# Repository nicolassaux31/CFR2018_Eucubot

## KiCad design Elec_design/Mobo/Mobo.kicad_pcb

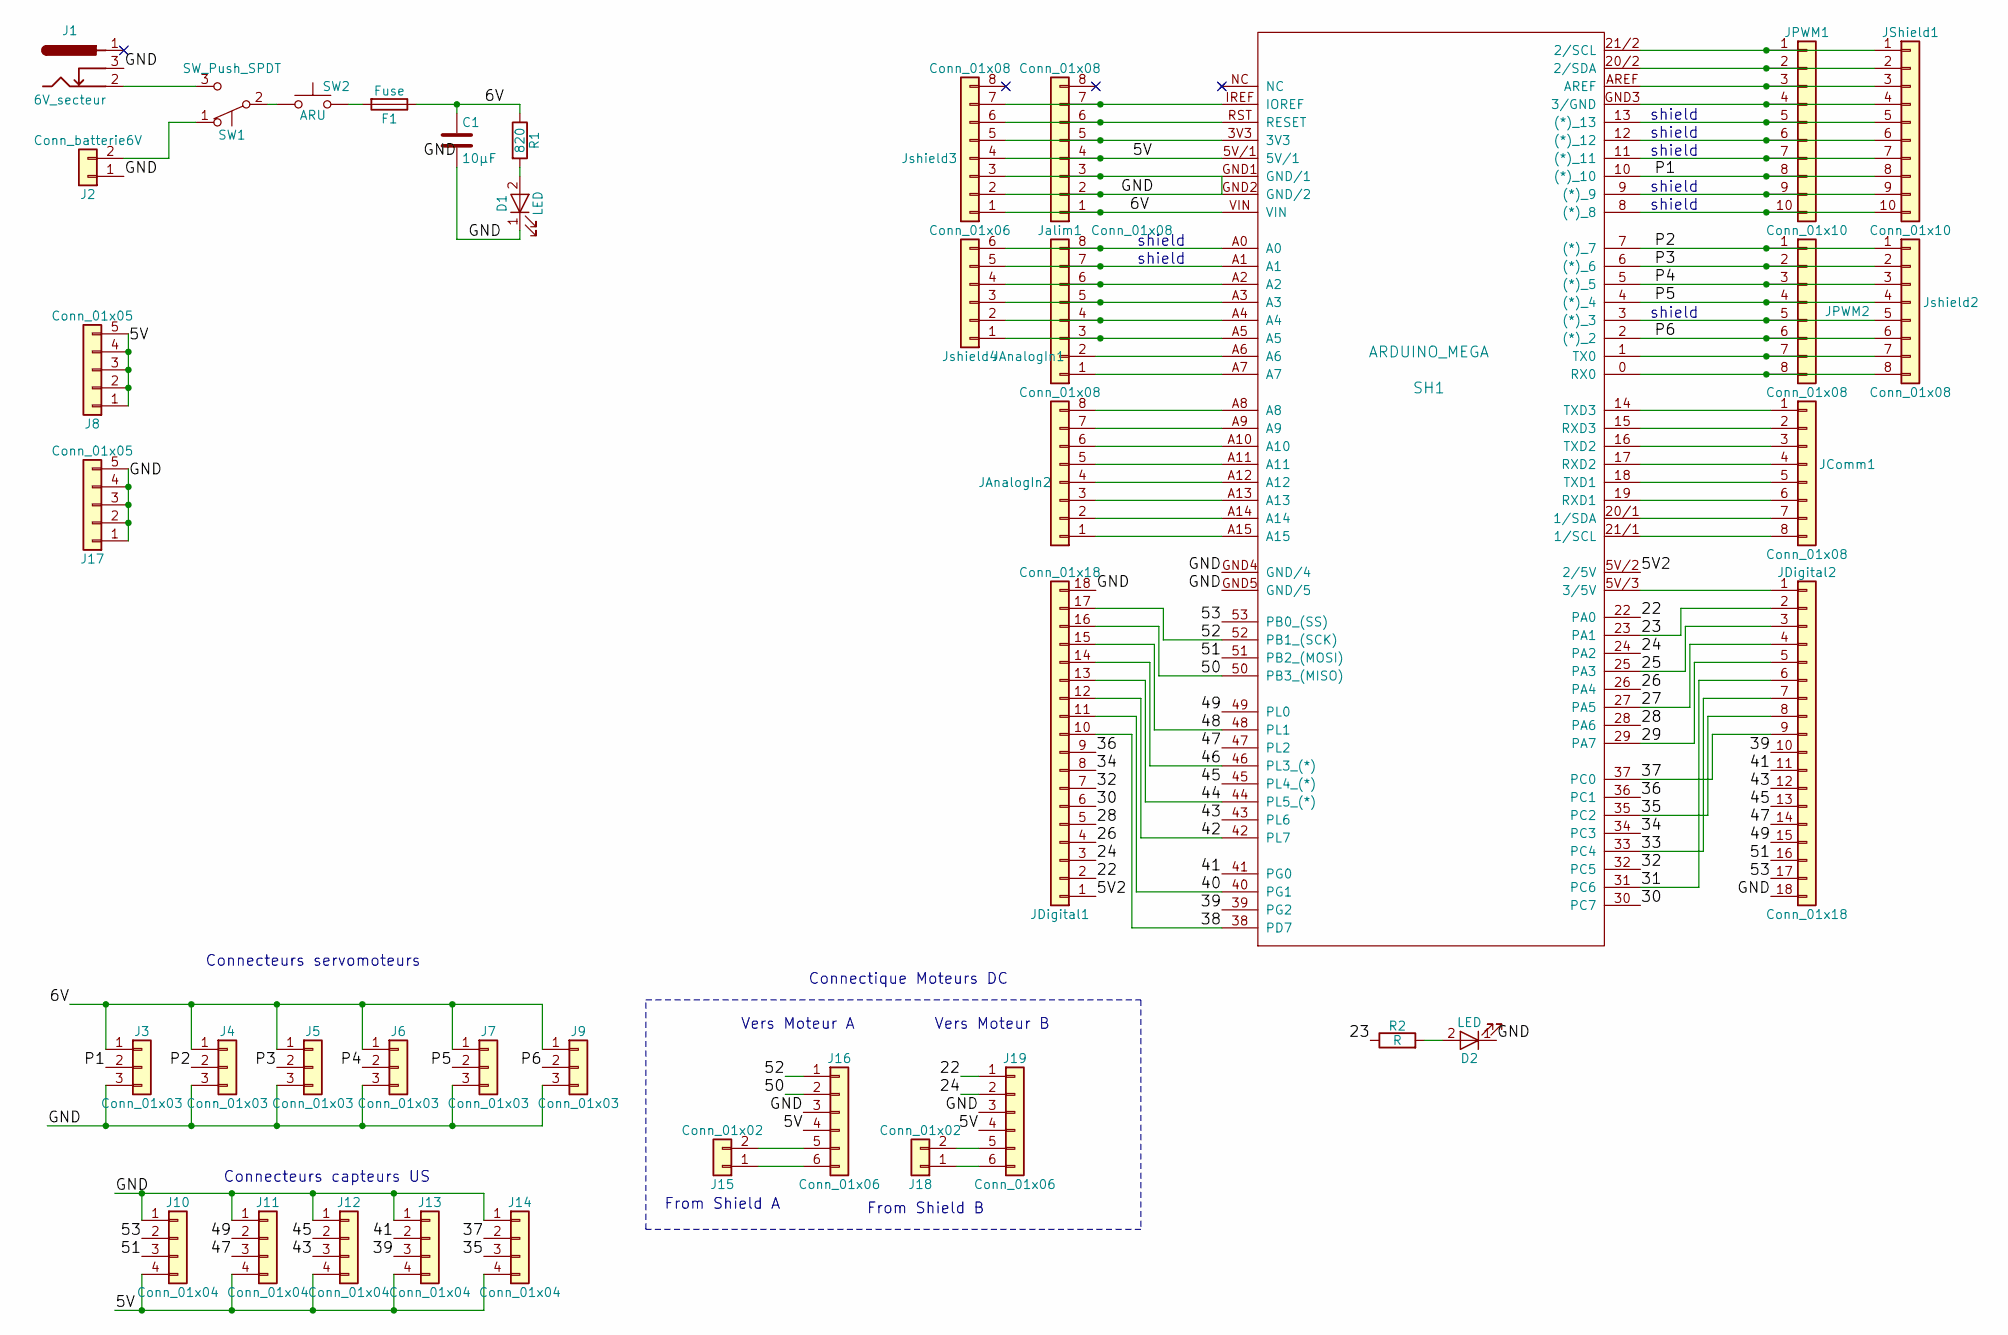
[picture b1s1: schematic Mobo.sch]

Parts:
C1: 10µF; C_Rect_L7.0mm_W2.0mm_P5.00mm
D1, D2: LED; LED_D5.0mm
F1: Fuse; R_Axial_Power_L25.0mm_W6.4mm_P30.48mm
J1: 6V_secteur; BARREL_JACK
J2: Conn_batterie6V; conn_2_5.08
J3, J4, J5, J6, J7, J9: Conn_01x03; Conn_1x3_3.81
J8, J17: Conn_01x05; Pin_Header_Straight_1x05_Pitch2.54mm
J10, J11, J12, J13, J14: Conn_01x04; conn_4_3.81
J15, J18: Conn_01x02; Pin_Header_Straight_1x02_Pitch2.54mm
J16, J19: Conn_01x06; Pin_Header_Straight_1x06_Pitch2.00mm
JAnalogIn1, JAnalogIn2: Conn_01x08; Socket_Strip_Straight_1x08_Pitch2.54mm
JComm1: Conn_01x08; Socket_Strip_Straight_1x08_Pitch2.54mm
JDigital1, JDigital2: Conn_01x18; Socket_Strip_Straight_1x18_Pitch2.54mm
JPWM1: Conn_01x10; Socket_Strip_Straight_1x10_Pitch2.54mm
JPWM2: Conn_01x08; Socket_Strip_Straight_1x08_Pitch2.54mm
JShield1: Conn_01x10; Socket_Strip_Straight_1x10_Pitch2.54mm
Jalim1: Conn_01x08; Pin_Header_Straight_1x08_Pitch2.54mm
Jshield2, Jshield3: Conn_01x08; Socket_Strip_Straight_1x08_Pitch2.54mm
Jshield4: Conn_01x06; Socket_Strip_Straight_1x06_Pitch2.54mm
R1: 820; R_Axial_DIN0411_L9.9mm_D3.6mm_P15.24mm_Horizontal
R2: R; R_Axial_DIN0411_L9.9mm_D3.6mm_P15.24mm_Horizontal
SH1: ARDUINO_MEGA; ARDUINO_MEGA_2560_R3_CONTOUR_ELL
SW1: SW_Push_SPDT; Conn_1x3_3.81
SW2: ARU; conn_2_5.08

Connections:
/5V: J8.1, J8.2, J8.3, J8.4, J8.5, J10.4, J11.4, J12.4, J13.4, J14.4, J16.4, J19.4, Jalim1.4, Jshield3.4, SH1.5V/1
/5V2: JDigital1.1, SH1.5V/2 (2/5V)
/6V: C1.1, F1.1, J3.1, J4.1, J5.1, J6.1, J7.1, J9.1, Jalim1.1, Jshield3.1, R1.1, SH1.VIN
/22: J19.1, JDigital1.2, SH1.22 (PA0)
/23: JDigital2.2, R2.1, SH1.23 (PA1)
/24: J19.2, JDigital1.3, SH1.24 (PA2)
/25: JDigital2.3, SH1.25 (PA3)
/26: JDigital1.4, SH1.26 (PA4)
/27: JDigital2.4, SH1.27 (PA5)
/28: JDigital1.5, SH1.28 (PA6)
/29: JDigital2.5, SH1.29 (PA7)
/30: JDigital1.6, SH1.30 (PC7)
/31: JDigital2.6, SH1.31 (PC6)
/32: JDigital1.7, SH1.32 (PC5)
/33: JDigital2.7, SH1.33 (PC4)
/34: JDigital1.8, SH1.34 (PC3)
/35: J14.3, JDigital2.8, SH1.35 (PC2)
/36: JDigital1.9, SH1.36 (PC1)
/37: J14.2, JDigital2.9, SH1.37 (PC0)
/38: JDigital1.10, SH1.38 (PD7)
/39: J13.3, JDigital2.10, SH1.39 (PG2)
/40: JDigital1.11, SH1.40 (PG1)
/41: J13.2, JDigital2.11, SH1.41 (PG0)
/42: JDigital1.12, SH1.42 (PL7)
/43: J12.3, JDigital2.12, SH1.43 (PL6)
/44: JDigital1.13, SH1.44 (PL5_(*))
/45: J12.2, JDigital2.13, SH1.45 (PL4_(*))
/46: JDigital1.14, SH1.46 (PL3_(*))
/47: J11.3, JDigital2.14, SH1.47 (PL2)
/48: JDigital1.15, SH1.48 (PL1)
/49: J11.2, JDigital2.15, SH1.49 (PL0)
/50: J16.2, JDigital1.16, SH1.50 (PB3_(MISO))
/51: J10.3, JDigital2.16, SH1.51 (PB2_(MOSI))
/52: J16.1, JDigital1.17, SH1.52 (PB1_(SCK))
/53: J10.2, JDigital2.17, SH1.53 (PB0_(SS))
/GND: C1.2, D1.1 (K), D2.1 (K), J1.3, J2.1, J3.3, J4.3, J5.3, J6.3, J7.3, J9.3, J10.1, J11.1, J12.1, J13.1, J14.1, J16.3, J17.1, J17.2, J17.3, J17.4, J17.5, J19.3, JDigital1.18, JDigital2.18, Jalim1.2, Jalim1.3, Jshield3.2, Jshield3.3, SH1.GND1 (GND/1), SH1.GND2 (GND/2), SH1.GND4 (GND/4), SH1.GND5 (GND/5)
/P1: J3.2, JPWM1.8, JShield1.8, SH1.10 ((*)_10)
/P2: J4.2, JPWM2.1, Jshield2.1, SH1.7 ((*)_7)
/P3: J5.2, JPWM2.2, Jshield2.2, SH1.6 ((*)_6)
/P4: J6.2, JPWM2.3, Jshield2.3, SH1.5 ((*)_5)
/P5: J7.2, JPWM2.4, Jshield2.4, SH1.4 ((*)_4)
/P6: J9.2, JPWM2.6, Jshield2.6, SH1.2 ((*)_2)
unnamed: D1.2 (A), R1.2
unnamed: D2.2 (A), R2.2
unnamed: F1.2, SW2.2
unnamed: J1.2, SW1.3 (C)
unnamed: J2.2, SW1.1 (A)
unnamed: J15.1, J16.6
unnamed: J15.2, J16.5
unnamed: J18.1, J19.6
unnamed: J18.2, J19.5
unnamed: JAnalogIn1.1, SH1.A7
unnamed: JAnalogIn1.2, SH1.A6
unnamed: JAnalogIn1.3, Jshield4.1, SH1.A5
unnamed: JAnalogIn1.4, Jshield4.2, SH1.A4
unnamed: JAnalogIn1.5, Jshield4.3, SH1.A3
unnamed: JAnalogIn1.6, Jshield4.4, SH1.A2
unnamed: JAnalogIn1.7, Jshield4.5, SH1.A1
unnamed: JAnalogIn1.8, Jshield4.6, SH1.A0
unnamed: JAnalogIn2.1, SH1.A15
unnamed: JAnalogIn2.2, SH1.A14
unnamed: JAnalogIn2.3, SH1.A13
unnamed: JAnalogIn2.4, SH1.A12
unnamed: JAnalogIn2.5, SH1.A11
unnamed: JAnalogIn2.6, SH1.A10
unnamed: JAnalogIn2.7, SH1.A9
unnamed: JAnalogIn2.8, SH1.A8
unnamed: JComm1.1, SH1.14 (TXD3)
unnamed: JComm1.2, SH1.15 (RXD3)
unnamed: JComm1.3, SH1.16 (TXD2)
unnamed: JComm1.4, SH1.17 (RXD2)
unnamed: JComm1.5, SH1.18 (TXD1)
unnamed: JComm1.6, SH1.19 (RXD1)
unnamed: JComm1.7, SH1.20/1 (1/SDA)
unnamed: JComm1.8, SH1.21/1 (1/SCL)
unnamed: JDigital2.1, SH1.5V/3 (3/5V)
unnamed: JPWM1.1, JShield1.1, SH1.21/2 (2/SCL)
unnamed: JPWM1.2, JShield1.2, SH1.20/2 (2/SDA)
unnamed: JPWM1.3, JShield1.3, SH1.AREF
unnamed: JPWM1.4, JShield1.4, SH1.GND3 (3/GND)
unnamed: JPWM1.5, JShield1.5, SH1.13 ((*)_13)
unnamed: JPWM1.6, JShield1.6, SH1.12 ((*)_12)
unnamed: JPWM1.7, JShield1.7, SH1.11 ((*)_11)
unnamed: JPWM1.9, JShield1.9, SH1.9 ((*)_9)
unnamed: JPWM1.10, JShield1.10, SH1.8 ((*)_8)
unnamed: JPWM2.5, Jshield2.5, SH1.3 ((*)_3)
unnamed: JPWM2.7, Jshield2.7, SH1.1 (TX0)
unnamed: JPWM2.8, Jshield2.8, SH1.0 (RX0)
unnamed: Jalim1.5, Jshield3.5, SH1.3V3
unnamed: Jalim1.6, Jshield3.6, SH1.RST (RESET)
unnamed: Jalim1.7, Jshield3.7, SH1.IREF (IOREF)
unnamed: SW1.2 (B), SW2.1

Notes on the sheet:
shield
Connectique Moteurs DC
Connecteurs servomoteurs
Connecteurs capteurs US
From Shield A
Vers Moteur A
Vers Moteur B
From Shield B

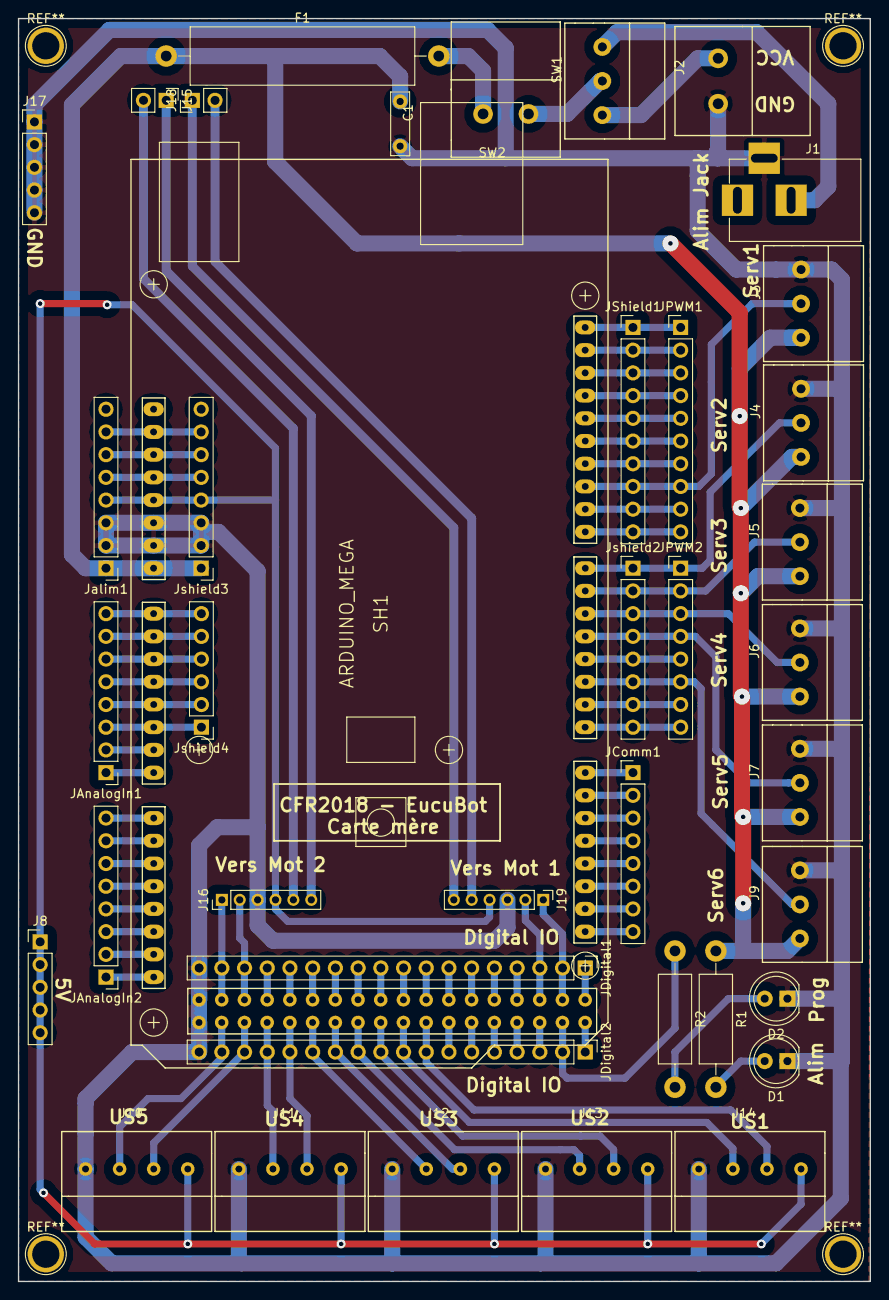
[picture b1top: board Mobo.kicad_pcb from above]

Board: 2 copper layers, 95.2 x 141.2 mm, 40 parts (0 on the bottom side), 92 nets.

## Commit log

2018-02-11 Create first version of test
2018-02-11 Changement sur txt 1
2018-02-11 Premier changement branche
2018-02-11 Bonjour--> Salut
2018-02-11 Salut-->Bonjour
2018-02-11 Salut-->Yo
2018-02-11 Lignes entre changement 1 et chang branche 1
2018-02-11 Lignes pour creer conflict lors de fusion
2018-02-11 test pulls changements
2018-02-11 Création nouveau test
2018-02-11 changement sur test2
2018-02-11 changement sur lequel on voudra revenir
2018-02-11 suppression du changement sur lequel on voulait revenir
2018-02-11 test modifs sur catpart
2018-02-11 test modifs sur catpart ça marche
2018-02-11 Changement de piece sur branche
2018-02-11 Création de dossier pour fichier tests tutos git
2018-02-11 ajout txt avec commandes utiles
2018-02-11 Actualization pre-pull
2018-02-11 fixes #2, resou bug signalé
2018-02-11 Ajout commandes git
2018-03-06 Traduction commandes 2
2018-03-06 Traduction commandes 3
2018-03-07 Je teste la commande commit tout cours
2018-03-07 Preparation fichiers fablab abeille, balles et interrupteur
2018-03-10 Test Remi
2018-03-10 test 2
2018-03-10 Ajout elec design
    Cartes elec sur kicad
2018-03-11 Test Branch
    test
2018-03-11 Modification carte mère
    Prise en compte de la taille des composants sur la carte
    Modification d'empreinte
    Ajustements
    Ajout d'une led à programmer pour débugger
2018-03-14 Commandes git traduites
2018-03-14 Premier modèle abeille pour tests roulements, et agrandissement de l'embase
    - Changements:
    Périmetre embase augmenté de 800 à 1000mm environ.
    Trous sur embase pour cablages moteurs.
    Creation fichiers design abeille.
    - Resultat:
    Les roulements fonctionnent
2018-03-20 Ajout nouveaus fichiers abeille
2018-03-20 Changement test
2018-03-20 Finalisation de l'abeille et premier prototype premier étage
    Changements:
    - Amelioration des parties de l'abeille déjà dessinée (réduction
    du bois en contact avec la pente).
    - Création parties abeille: aile, partie aiguille, partie poids.
    - Création de premier prototype pour le premier étage.
    Résultats:
2018-03-21 Correction de commit antérieur, la base doit être changée sur le master ou une autre branche
2018-03-21 Creation premier prototype pour le premier étage
2018-03-23 Finalisation design carré pour le ballon et début assemblage abeille:
    - Dessin du carré pour le ballon en supposant 2cm d'épaisseur de
    chaque côté.
    - Inclusion de la pante dans le .product de l'abeille.
    Reste à ameliorer l'abeille avant l'assemblage de tout, auquel on pourra
    ajouter le bras du moteur.
2018-03-23 Actualisation fichiers base
2018-03-23 Changement fichiers embase pour utilisation correcte git
2018-03-23 Assemblage étages et parechoques sur product général Robot
2018-03-25 Create Catapulte
2018-03-25 Catapulte
    Création des parties de la catapulte. Pièces Solidworks / Assemblage / Pièces DXF
2018-03-26 Pièces du bras (suite)
    Ajouts des pièces en 3D du bras pour récupérer les balles / fichier DXF des pièces manquantes / Aperçu 3D du bras final
2018-03-28 Modification
    Ajouts / Modifications pièces DXF
2018-03-28 Pièces DXF
2018-03-28 Modification
2018-03-28 Amelioration de l'abeille: - Inclusion deuxième roue. - Élargissement de l'aile des deux côtés. - Système d'accrochage Aiguille. - Box ballon.
2018-03-28 Premier modèle de l'abeille complet:
    Dernier commit était déjà complet mais avec pièce mal conçue, corrigée sur
    celui-ci.
2018-03-28 Création Panneau Domotique
    Création du dossier Panneau domotique :
    - Logo Ense3 en format solidworks 3D
    - Logo Ense3 en format mise en plan
    - Logo Ense3 au format DXF (Taille environ 380x245 mm)
2018-04-04 Finalisation abeille
2018-04-05 Changement de l'embase et nouveau assemblage: - Création mécanisme CATIA sur l'interruption. - Placement interrupteur sur étage bas. - Cŕéation de chasseneiges. - Ajout pièces déjà conçues mais manqu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
2018-04-06 Modification catapulte & bras
    Bras récupérateur (inchangé):
    - Fichiers DXF ("BrasPartie1" & "BrasPartie2")
    - Le dossier "Images" contient une capture d'écran de l'assemblage Solidworks du bras.
    Catapulte (modifié) :
    - Fichier DXF ("CatapulteV2")
    - Le dossier "Images" contient une capture d'écran de l'assemblage Solidworks de la catapulte.
2018-04-06 Ajout d'éléments au product global du robot: - Roulements à billes. - Création du modèle CATIA du bras collecteur.
2018-04-09 Nouvelle version du Bras
    Nouveau bras (non définitif)
    -Ajout des pièces 3D Solidworks + assemblage
    -Ajout de l'assemblage STEP 203
    -Retrait des anciens éléments
2018-04-10 Commencement premier prototype:
    - Assemblage système lancement balles.
    - Création 3ème étage avec entretoits longs.
    - Premier prototype aiguillage
2018-04-10 Mise à jour des fichiers catapulte & bras
    - Modifications des pièces du bras et de la catapulte
    - Ajouts des fichiers STEP les plus récents
2018-04-10 Création d'un support panneau domotique
    Sert à tenir la plaque de plexi et la batterie (type nimh) le tout maintenant contre le chateau d'eau
2018-04-11 Ajout pièces à assemblage général: - Positionnement définitif catapulte (prototype 1). - Modélisation moteur catapulte et positionnement. - Ajout nouveau bras. - Création dossiers bras abeille.
2018-04-11 Changement routage parts bras abeille
2018-04-24 Ajout de la section due code ARDUINO
    - Code principale du robot
    - Ajout de la bibliothèque pour la compatibilité avec servo
    -Fichier .txt pour les démarches
2018-04-27 Ajout de la dernière version du code
2018-05-02 PROTOTYPE 1 FINAL: CARA CUP
2018-05-02 Ajout des nouveaux codes pour l'homologation
2018-05-04 Modification code arduino (SHARP)
2018-05-11 Ajout code CFR fonctionnel
2018-05-16 Ajout du code du Challenge de Robotique
    Action effectuée par le code :
    -Interrupteur
    -Abeille
    -Pousser quelques blocs dans la zone
2018-05-22 Finission du deuxième prototype. Changements: - Nouveau système de guidage des balles. - Bras récupérateur plus incliné. - Nouveau système de catapulte (roue+DC controlé en vitesse par PWM). - Petite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
